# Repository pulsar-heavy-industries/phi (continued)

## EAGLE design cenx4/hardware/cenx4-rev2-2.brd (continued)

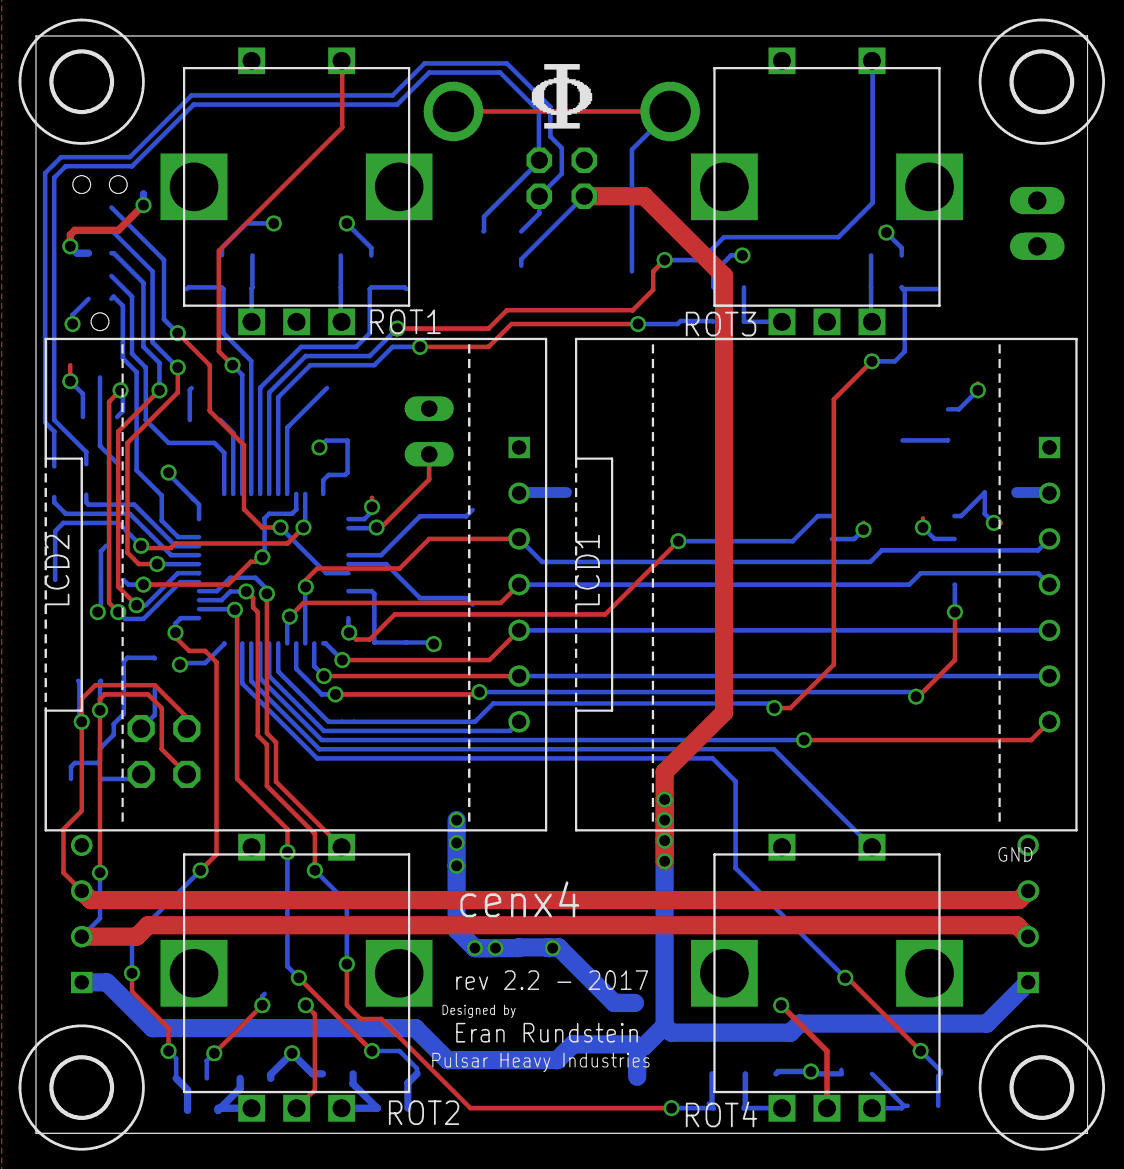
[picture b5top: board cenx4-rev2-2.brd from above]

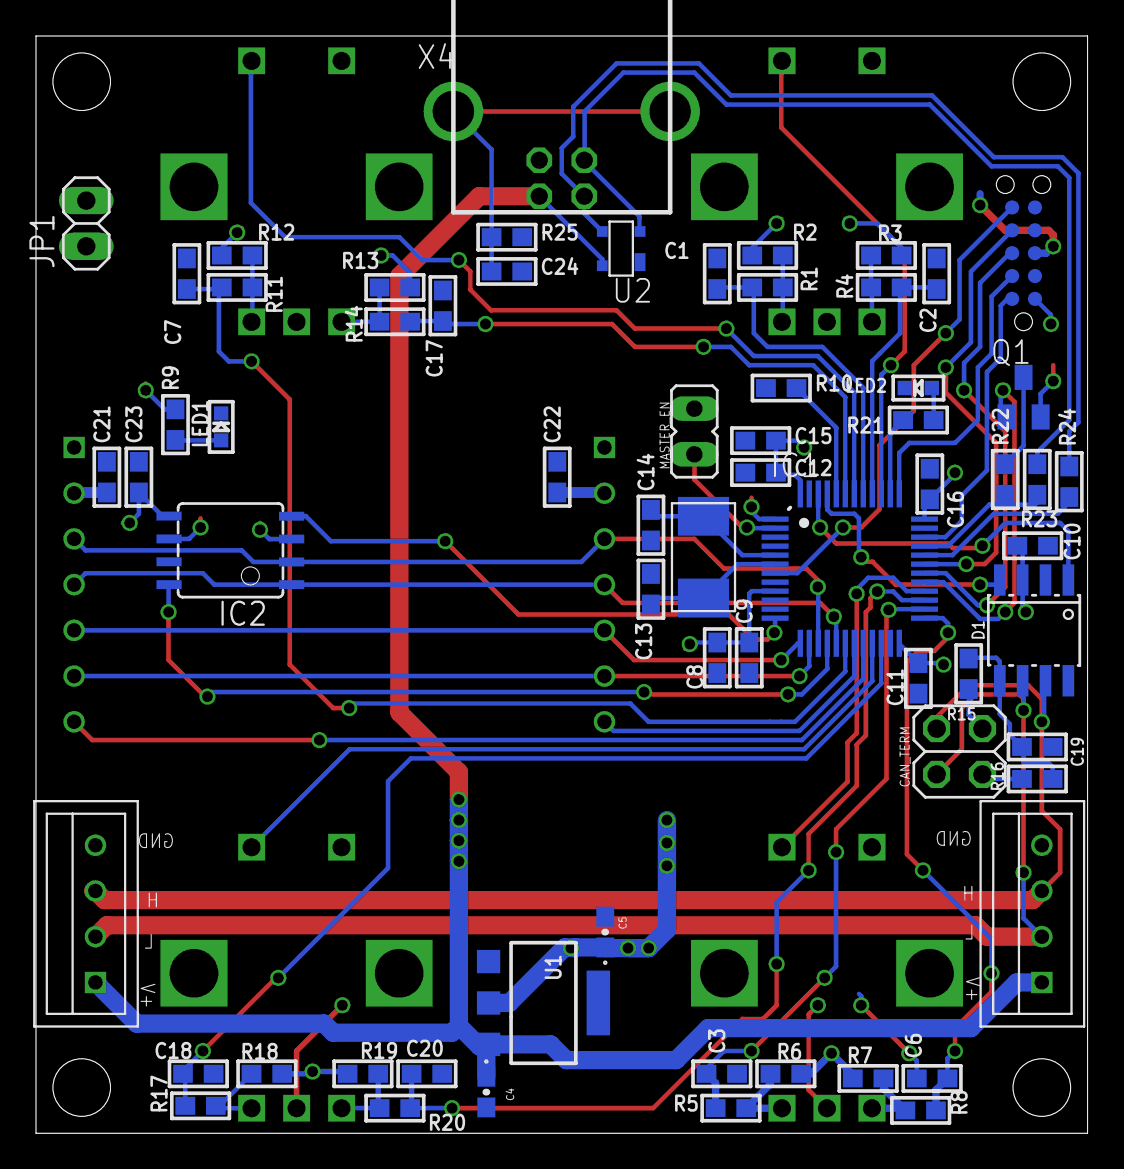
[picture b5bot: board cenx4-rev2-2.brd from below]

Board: 2 copper layers, 58.4 x 61.0 mm, 75 parts (65 on the bottom side), 57 nets.

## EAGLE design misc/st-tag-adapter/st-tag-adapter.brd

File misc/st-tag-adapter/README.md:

A tiny adapter board that makes it easier to use a [Tag-Connect TC2050-IDC](http://www.tag-connect.com/TC2050-IDC) cable with an ST evaluation kit such as the [STM32F4DISCOVERY](http://www.st.com/en/evaluation-tools/stm32f4discovery.html).

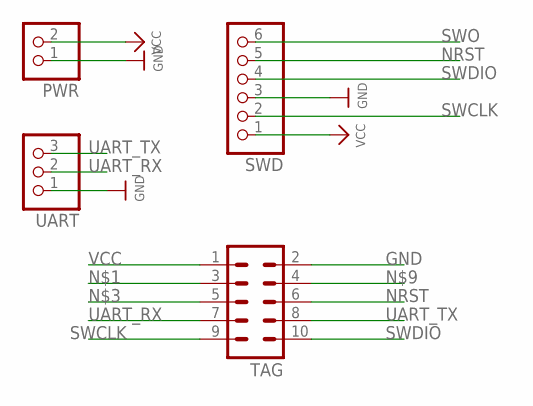
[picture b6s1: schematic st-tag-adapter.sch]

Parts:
PWR: HEADER-1X2ROUND; 1X02_ROUND
SWD: HEADER-1X6ROUND; 1X06_ROUND
TAG: ML10
UART: HEADER-1X3ROUND; 1X03_ROUND

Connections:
GND: PWR.1, SWD.3, TAG.2, UART.1
NRST: SWD.5, TAG.6
SWCLK: SWD.2, TAG.9
SWDIO: SWD.4, TAG.10
SWO: SWD.6
UART_RX: TAG.7, UART.2
UART_TX: TAG.8, UART.3
VCC: PWR.2, SWD.1, TAG.1

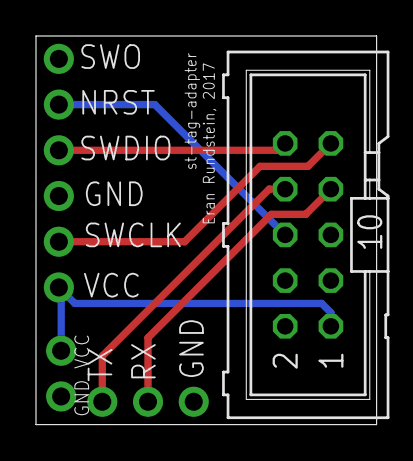
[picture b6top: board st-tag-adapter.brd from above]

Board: 2 copper layers, 18.9 x 21.6 mm, 4 parts (0 on the bottom side), 7 nets.

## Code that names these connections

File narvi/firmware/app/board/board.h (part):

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/*
 * GPIOA setup:
 *
 * PA0  - BUTTON                    (input floating).
 * PA1  - MEMS_INT1                 (input floating).
 * PA2  - MEMS_INT2                 (input floating).
 * PA3  - LCD_B5                    (alternate 14).
 * PA4  - LCD_VSYNC                 (alternate 14).
 * PA5  - PIN5                      (input pullup).
 * PA6  - LCD_G2                    (alternate 14).
 * PA7  - ACP_RST                   (input pullup).
 * PA8  - I2C3_SCL                  (alternate 4).
 * PA9  - UART_TX                   (alternate 7).
 * PA10 - UART_RX                   (alternate 7).
 * PA11 - LCD_R4                    (alternate 14).
 * PA12 - LCD_R5                    (alternate 14).
 * PA13 - SWDIO                     (alternate 0).
 * PA14 - SWCLK                     (alternate 0).
 * PA15 - TP_INT                    (input floating).
 */
#define VAL_GPIOA_MODER             (PIN_MODE_INPUT(GPIOA_I2S_CKIN) |         \
                                     PIN_MODE_INPUT(GPIOA_PIN1) |      \
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/*
 * GPIOB setup:
 *
 * PB0  - LCD_R3                    (alternate 14).
 * PB1  - LCD_R6                    (alternate 14).
 * PB2  - BOOT1                     (input pullup).
 * PB3  - SWO                       (alternate 0).
 * PB4  - PIN4                      (input pullup).
 * PB5  - FMC_SDCKE1                (alternate 12).
 * PB6  - FMC_SDNE1                 (alternate 12).
 * PB7  - PIN7                      (input pullup).
 * PB8  - LCD_B6                    (alternate 14).
 * PB9  - LCD_B7                    (alternate 14).
 * PB10 - LCD_G4                    (alternate 14).
 * PB11 - LCD_G5                    (alternate 14).
 * PB12 - OTG_HS_ID                 (alternate 12).
 * PB13 - OTG_HS_VBUS               (input pulldown).
 * PB14 - OTG_HS_DM                 (alternate 12).
 * PB15 - OTG_HS_DP                 (alternate 12).
 */
#define VAL_GPIOB_MODER             (PIN_MODE_ALTERNATE(GPIOB_ROT2_SW) |     \
                                     PIN_MODE_ALTERNATE(GPIOB_ROT2_A) |     \
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 *
 * PC0  - FMC_SDNWE                 (alternate 12).
 * PC1  - SPI5_MEMS_CS              (output pushpull maximum).
 * PC2  - SPI5_LCD_CS               (output pushpull maximum).
 * PC3  - PIN3                      (input pullup).
 * PC4  - OTG_HS_PSO                (output pushpull maximum).
 * PC5  - OTG_HS_OC                 (input floating).
 * PC6  - LCD_HSYNC                 (alternate 14).
 * PC7  - LCD_G6                    (alternate 14).
 * PC8  - PIN8                      (input pullup).
 * PC9  - I2C3_SDA                  (alternate 4).
 * PC10 - LCD_R2                    (alternate 14).
 * PC11 - PIN11                     (input pullup).
 * PC12 - PIN12                     (input pullup).
 * PC13 - PIN13                     (input pullup).
 * PC14 - OSC32_IN                  (input floating).
 * PC15 - OSC32_OUT                 (input floating).
 */
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/*
 * GPIOD setup:
 *
 * PD0  - FMC_D2                    (alternate 12).
 * PD1  - FMC_D3                    (alternate 12).
 * PD2  - PIN2                      (input pullup).
 * PD3  - LCD_G7                    (alternate 14).
 * PD4  - PIN4                      (input pullup).
 * PD5  - PIN5                      (input pullup).
 * PD6  - LCD_B2                    (alternate 14).
 * PD7  - PIN7                      (input pullup).
 * PD8  - FMC_D13                   (alternate 12).
 * PD9  - FMC_D14                   (alternate 12).
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 *
 * PE0  - FMC_NBL0                  (alternate 12).
 * PE1  - FMC_NBL1                  (alternate 12).
 * PE2  - PIN2                      (input pullup).
 * PE3  - PIN3                      (input pullup).
 * PE4  - PIN4                      (input pullup).
 * PE5  - PIN5                      (input pullup).
 * PE6  - PIN6                      (input pullup).
 * PE7  - FMC_D4                    (alternate 12).
 * PE8  - FMC_D5                    (alternate 12).
 * PE9  - FMC_D6                    (alternate 12).
 * PE10 - FMC_D7                    (alternate 12).
 * PE11 - FMC_D8                    (alternate 12).
 * PE12 - FMC_D9                    (alternate 12).
 * PE13 - FMC_D10                   (alternate 12).
 * PE14 - FMC_D11                   (alternate 12).
 * PE15 - FMC_D12                   (alternate 12).
 */
#define VAL_GPIOE_MODER             (PIN_MODE_ALTERNATE(GPIOE_PIN0) |   \
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 * PG4  - FMC_BA0                   (alternate 12).
 * PG5  - FMC_BA1                   (alternate 12).
 * PG6  - LCD_R7                    (alternate 14).
 * PG7  - LCD_CLK                   (alternate 14).
 * PG8  - FMC_SDCLK                 (alternate 12).
 * PG9  - PIN9                      (input pullup).
 * PG10 - LCD_G3                    (alternate 14).
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/*
 * GPIOH setup:
 *
 * PH0  - OSC_IN                    (input floating).
 * PH1  - OSC_OUT                   (input floating).
 * PH2  - PIN2                      (input pullup).
 * PH3  - PIN3                      (input pullup).
 * PH4  - PIN4                      (input pullup).
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
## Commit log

2017-03-11 CAN CLEANUP - also adds crc16 which might slow things :(
2017-03-11 small cleanups
2017-03-11 midi cleanups
2017-03-11 junk
2017-03-11 todo cleanups
2017-03-11 io cleanup on cenx4
2017-03-12 cenx4_ui: move to using builtin ugfx arc stuff
2017-03-13 cenx4: set correct can dev_id
2017-03-13 phi_lib: fix can crc checking
2017-03-13 cenx4: make module mapping work in ableton app
2017-03-13 cenx4: ghetto app log, cenx4_ui app mode
2017-03-13 cenx4: almost make modules optional
2017-03-15 cenx4: initial ableton commit
2017-03-15 cenx4: ableton scripts: change parameter release strategy
2017-03-15 cenx4: ableton: throttle updates to make everything more responsive
2017-03-15 cenx4: ableton: cleanup used stuff
2017-03-15 cenx4: ableton: misc cleanups
2017-03-15 cenx4: midi device names cleanup
2017-03-15 add vendor dir
2017-03-15 cenx4: enable CENX4_MIDI_SYSEX_START_BOOTLOADER
2017-03-22 add TODO
2017-03-24 Cleanup bootloader build process
2017-03-24 update bootloader filenames in README
2017-03-25 add st-tag-adapter
2017-03-25 text updates
2017-03-25 typo
2017-03-25 add some sysex cmd to send both pot text and val at the same time
2017-03-25 cleanups
2017-03-25 get rid of Cenx4Mgr
2017-03-27 add cenx4_app_traktor
2017-03-27 cenx4_app_traktor improvements
2017-03-27 add ph-traktor.tsi
2017-03-28 hyperion initial commit
2017-04-05 renable locking in cenx4_ui
2017-04-07 cenx4: use GPIOA_USB_CONN
2017-04-07 cenx4: slave app initial commit
2017-04-07 cenx4: slave mode seems operational
2017-04-07 add reset cmd, MAYBE INTRODUCE RACE IN CAN
2017-04-07 cenx4: some bl groundwork
2017-04-07 cenx4: can bl poc works
2017-04-07 update TODO
2017-04-08 hyperion: basic bl->app functionality, io seems to work fine
2017-04-08 hyperion: more app infrastructure
2017-04-08 hyperion: adapt ui from cenx4
2017-04-09 hyperion: test app showing all hardware works
2017-04-09 hyperion: test app improvements
2017-04-09 hyperion+cenx4: controller->traktor works
2017-04-09 hyperion+cenx4: traktor 1 channel + cenx as master works
2017-04-09 hyperion+cenx4: encoders
2017-04-10 cenx4: switch pots range to 0-0xff
2017-04-10 cenx4: small cleanups
2017-04-10 cenx4: add can cmd to send both val and text
2017-04-10 cenx4: merge set disp+set dispmode into one command
2017-04-10 cenx4, hyperion: cleanup hw_sw_ver, use all 32 bits
2017-04-10 cenx4: use same usbcfg.c for bl and app
2017-04-10 initial commit of phi-www using create-react-app
2017-04-10 cenx4: web bl poc works
2017-04-10 cenx4: bootloading app cleanup
2017-04-11 cenx4: support for 3 boards, ableton resync command
2017-04-11 cenx4: move pot mapping to the ableton script
2017-04-12 remove some TODOs
2017-04-13 phi_lib: always send 4 byte usb midi packets
2017-04-13 remove old traktor file
2017-04-13 add cenx4 hw files
2017-04-13 add cenx4 enclosure files
2017-04-13 hyperion: add eagle files
2017-04-14 cenx4: ableton: add banks encoder support - allows using the last encoder as a bank selector
2017-04-14 cenx4: add some todos
2017-04-17 cenx4: slave encoder speed button support
2017-04-17 cenx4: use existing cfg when saving in setup app
2017-04-17 cenx4: dont share sysex command ids between apps
2017-04-17 cenx4: maybe fix lcd reset, speedup startup
2017-04-17 cenx4: make setup look for holes in module list
2017-04-27 add f429 openocd files
2017-05-12 Major changes to bootloading process: - Headers changed - Serial flash support on CENX4 - Multiimg support over serial flash
2017-05-14 hyperion: first enclosure iteration
2017-05-15 hyperion: add simple split pot ui mode
2017-05-15 let cenx4 map hyperion modules
2017-05-16 cenx4: improve traktor integration
2017-05-16 add shift mode to traktor mapping
2017-05-25 hyperion: update traktor mapping to light up the "load track to deck" button in browse mode
2017-05-25 cenx4: add startup app configuration, re-arrange traktor browse controls layout
2017-05-25 cenx4: small change to traktor browse mode ui
2017-05-25 cenx4: add preview encoder to traktor browse mode
2017-05-25 hyperion: fix pot rendering issue
2017-05-25 cenx4: basic traktor loop support
2017-05-27 cenx4: traktor: rename shift1 mode to cue, make cue mode/button toggle instead of hole, exit browse page and stop preview player once a track is loaded
2017-06-06 use pid.codes vid/pid
2017-06-27 add misc/ugfx-ssd1306-scrshot.py
2017-07-14 README work
2017-07-14 hyperion readme
2017-09-16 narvi wip
2017-09-16 temp disable lcd
2017-09-16 wip cleanups, nicer vu lcd
2017-09-16 wip - lcd working, audio working
2017-09-16 ext<->usb midi fwding works but without sysex
2017-09-16 ext/ctrl ports, usb->serial midi works, need to do other direction
2017-09-16 bl dat shit
2017-09-16 cleanup serial midi code, cleanup usb descriptor and set channel name strings for headphones
2017-09-16 midi with correct port names
2017-09-16 usb midi: have 2 in/out ports
2017-09-16 usb midi: 2 out, still need 2 in
2017-09-16 Narvi v0 (#1)
    Initial commit of Narvi stuff
2017-09-16 fix typo
2017-09-16 cenx4: add multi-img build target
2017-09-16 narvi: bunch of small cleanups
2017-09-16 narvi: more cleanups
2017-09-22 switch to ableton 9.7.4
2017-09-28 hyperion ableton: bindable volume slider per hyperion channel
2017-09-28 hyperion ableton: channel meter output
2017-09-28 hyperion ableton: ability to bind to tracks inside drum rack
2017-09-29 hyperion ableton: identify mapper devices
2017-09-29 hyperion ableton: basic track binding (without title) using hyperion
2017-09-29 hyperion ableton: v0 of track name sync
2017-09-29 hyperion ableton: vu meter and pot mapping works
2017-09-29 hyperion ableton: buttons work, v0 of POC done
2017-09-29 hyperion ableton: use encoder button to select track
2017-10-03 hyperion ableton: done die if telnet port already in use
2017-10-04 hyperion ableton: add resync on app start
2017-10-13 narvi: debugging dac losing byte sync (needs cleanup)
2017-10-13 cenx4 ableton2 configuration wip
2017-10-26 narvi: add narvi-ctrl eagle files
